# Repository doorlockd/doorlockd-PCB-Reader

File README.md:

## License
Copyright 2021-2025 Matthijs Kooijman (matthijs@stdin.nl)

This source describes Open Hardware and is licensed under the CERN-OHL-P
v2 or any later version.

You may redistribute and modify this documentation and make products
using it under the terms of the CERN-OHL-P v2 (https:/cern.ch/cern-ohl).

This documentation is distributed WITHOUT ANY EXPRESS OR IMPLIED
WARRANTY, INCLUDING OF MERCHANTABILITY, SATISFACTORY QUALITY AND FITNESS
FOR A PARTICULAR PURPOSE. Please see the CERN-OHL-P v2 for applicable
conditions

See LICENSE.txt for the full license text.

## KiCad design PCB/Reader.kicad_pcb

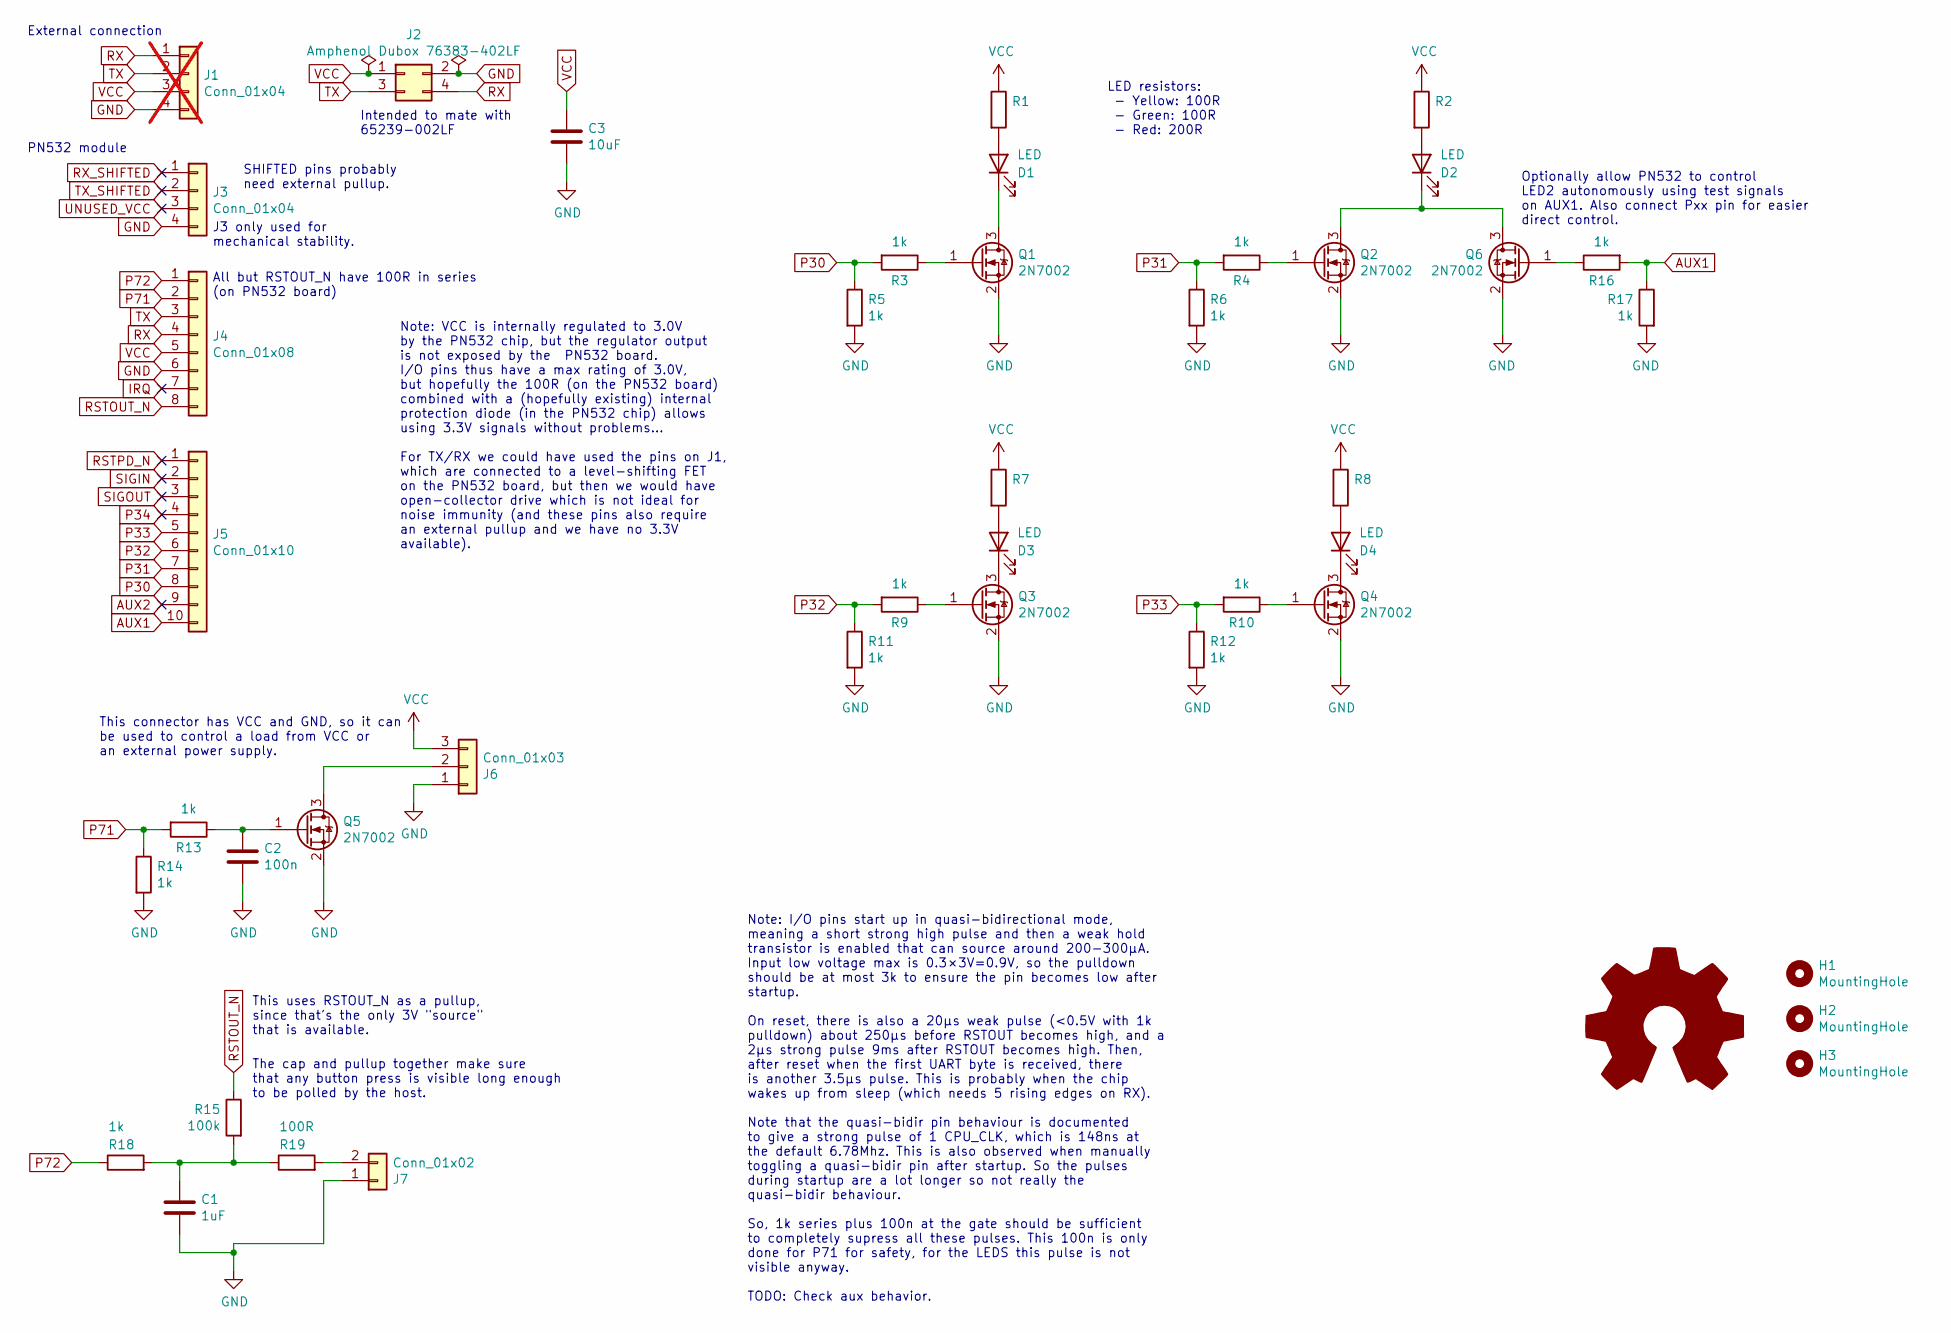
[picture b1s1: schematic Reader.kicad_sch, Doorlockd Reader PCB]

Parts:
C1: 1uF; C_0805_2012Metric_Pad1.18x1.45mm_HandSolder
C2: 100n; C_0805_2012Metric_Pad1.18x1.45mm_HandSolder
C3: 10uF; C_0805_2012Metric_Pad1.18x1.45mm_HandSolder
D1, D2, D3, D4: LED; LED_Rectangular_W5.0mm_H2.0mm
H1, H2, H3: MountingHole; MountingHole_3.2mm_M3
J1: Conn_01x04; PinHeader_1x04_P2.54mm_Vertical; not fitted
J2: Amphenol Dubox ‎76383-402LF‎; PinHeader_2x02_P2.54mm_Horizontal
J3: Conn_01x04; PinSocket_1x04_P2.54mm_Vertical
J4: Conn_01x08; PinSocket_1x08_P2.54mm_Vertical
J5: Conn_01x10; PinSocket_1x10_P1.27mm_Vertical
J6: Conn_01x03; PinHeader_1x03_P2.54mm_Horizontal
J7: Conn_01x02; PinHeader_1x02_P2.54mm_Horizontal
LOGO1: Logo_Open_Hardware_Large; OSHW-Symbol_8.9x8mm_SilkScreen
Q1, Q2, Q3, Q4, Q5, Q6: 2N7002; SOT-23_Handsoldering
R1, R2, R7, R8: R_0805_2012Metric_Pad1.20x1.40mm_HandSolder
R3, R4, R5, R6, R9, R10, R11, R12, R13, R14, R16, R17, R18: 1k; R_0805_2012Metric_Pad1.20x1.40mm_HandSolder
R15: 100k; R_0805_2012Metric_Pad1.20x1.40mm_HandSolder
R19: 100R; R_0805_2012Metric_Pad1.20x1.40mm_HandSolder

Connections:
AUX1: J5.10, R16.2, R17.1
AUX2: J5.9
GND: C1.2, C2.2, C3.2, J1.4, J2.2, J3.4, J4.6, J6.1, J7.1, Q1.2 (S), Q2.2 (S), Q3.2 (S), Q4.2 (S), Q5.2 (S), Q6.2 (S), R5.2, R6.2, R11.2, R12.2, R14.2, R17.2
IRQ: J4.7
unnamed: C1.1, R15.2, R18.2, R19.1
unnamed: D1.2 (A), R1.2
unnamed: D1.1 (K), Q1.3 (D)
unnamed: D2.2 (A), R2.2
unnamed: D2.1 (K), Q2.3 (D), Q6.3 (D)
unnamed: D3.2 (A), R7.2
unnamed: D3.1 (K), Q3.3 (D)
unnamed: D4.2 (A), R8.2
unnamed: D4.1 (K), Q4.3 (D)
unnamed: J6.2, Q5.3 (D)
unnamed: J7.2, R19.2
unnamed: Q1.1 (G), R3.1
unnamed: Q2.1 (G), R4.1
unnamed: Q3.1 (G), R9.1
unnamed: Q4.1 (G), R10.1
unnamed: C2.1, Q5.1 (G), R13.1
unnamed: Q6.1 (G), R16.1
P30: J5.8, R3.2, R5.1
P31: J5.7, R4.2, R6.1
P32: J5.6, R9.2, R11.1
P33: J5.5, R10.2, R12.1
P34: J5.4
P71: J4.2, R13.2, R14.1
P72: J4.1, R18.1
RSTOUT_N: J4.8, R15.1
RSTPD_N: J5.1
RX: J1.1, J2.4, J4.4
RX_SHIFTED: J3.1
SIGIN: J5.2
SIGOUT: J5.3
TX: J1.2, J2.3, J4.3
TX_SHIFTED: J3.2
UNUSED_VCC: J3.3
VCC: C3.1, J1.3, J2.1, J4.5, J6.3, R1.1, R2.1, R7.1, R8.1

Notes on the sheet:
This connector has VCC and GND, so it can be used to control a load from VCC or an external power supply.
Note: VCC is internally regulated to 3.0V by the PN532 chip, but the regulator output is not exposed by the PN532 board. I/O pins thus have a max rating of 3.0V, but hopefully the 100R (on the PN532 board) combined with a (hopefully existing) internal protection diode (in the PN532 chip) allows usi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
LED resistors: - Yellow: 100R - Green: 100R - Red: 200R
Optionally allow PN532 to control LED2 autonomously using test signals on AUX1. Also connect Pxx pin for easier direct control.
This uses RSTOUT_N as a pullup, since that's the only 3V "source" that is available.
PN532 module
SHIFTED pins probably need external pullup.
The cap and pullup together make sure that any button press is visible long enough to be polled by the host.
Note: I/O pins start up in quasi-bidirectional mode, meaning a short strong high pulse and then a weak hold transistor is enabled that can source around 200-300μA. Input low voltage max is 0.3×3V=0.9V, so the pulldown should be at most 3k to ensure the pin becomes low after startup. On reset, there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
J3 only used for mechanical stability.
Intended to mate with 65239-002LF
All but RSTOUT_N have 100R in series (on PN532 board)
External connection

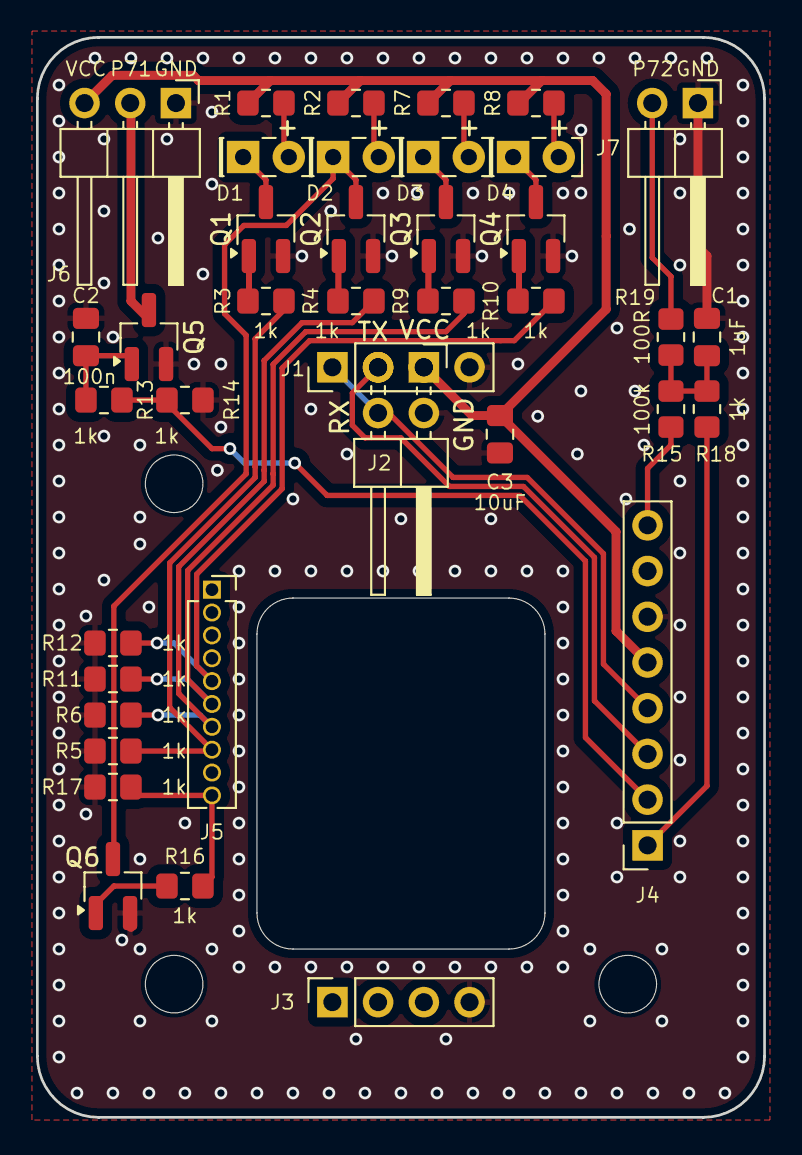
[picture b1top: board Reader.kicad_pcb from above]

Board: 2 copper layers, 40.4 x 60.0 mm, 43 parts (1 on the bottom side), 29 nets.

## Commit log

2021-02-20 Empty initial commit
2021-02-20 Add initial version v0.1
2023-06-06 Update schematic to KiCad 7
    This also sets the edge clearance to 0,5mm. This is a new setting, that
    was previously set using edge cuts line widths and/or zone clearance
    settings. This commit also refills the zones, which are slightly bigger
    than before.
    This also removes the old .sch and .pro file, which are replaced by
    .kicad_sch and .kicad_pro, and removes the lib cache, which is no longer
2023-06-06 Add board name and version to front silkscreen
2023-06-06 Make some schematic changes
    This adds some notes, updates some component values to the actually used
    values, and maybe some other small changes.
2024-01-23 Update PCB from schematic
    This makes no actual changes, just lets KiCad pull in changes (probably
    mostly udpated footprints and renumbered symbols, and maybe some KiCad
    upgrade changes too).
2024-01-23 Add 100n capacitor on output pin
    This takes care of suppressing the startup pulse given by the PN532.
2024-01-23 Add series resistors for button input
2024-02-03 Remove duplicate TODO
2024-02-06 Remove unintended silkscreen line
2024-02-06 Use hand soldering footprints for transistors
2024-02-06 Add input supply buffer cap
2024-02-06 Enlarge mounting holes
2024-02-06 Remove groundloop-related todos
    It seems that having multiple GND connections and a hole inside the GND
    plane might not actually be problematic (or if it is, making a horseshoe
    out of it might not make it better).
    So for now, leave this as is until it is actually a problem.
2024-02-06 Reduce overly wide thermal reliefs due to wide GND traces
    The thermal relief spoke width was 0,3mm, but there were also explicit
    GND traces of 0,5mm that made some components (esp C1 and some
    transistors) hard to solder. This reduces the trace width to 0,3mm,
    hopefully alleviating this issue.
2024-02-06 Mark LED polarity on silkscreen
2024-02-06 Clean up Fab layer
2024-05-28 Improve silkscreen layout
    This also moves some vias, locks some footprints and maybe makes some more changes.
2024-05-28 Update to KiCad 8
    This is the result of opening the project, schematic and board and the
    schematic setup and board setup dialogs (and clicking open each section)
    without making any changes. In addition, a zone fill is done.
    This commit changes all files completely, since the new KiCad adds more
    linebreaks to the files it writes.
2024-05-28 Add changelog file
2024-05-28 Move PCB files into new PCB subdirectory
    This gives a bit more structure to the repository and prepares for
    adding some workflow integration.
2024-05-28 PCB-workflows: Add submodule
2024-05-28 Set up PCB workflow
    This is the result of running `./PCB-workflows/tools/setup-project-repo.sh PCB/Reader.kicad_pro`
2024-10-09 DRC: Enlarge smallest silkscreen text
    The board setup, based on Aisler specifications, has minimum 0.8mm
    height for text. This changes most text that uses 0.75mm to use 0.8mm
    instead. No text is moved, this just enlarges the text slightly (by
    manually editing the kicad_pcb file).
2024-10-09 DRC: Exclude three GND pins with too few thermals
    These have a good connection on the bottom, just too little connection
    on the top, but since there is little GND plane on the top to connect
    to, this is not an issue.
2024-10-09 DRC: Remove random silkscreen lines
2024-10-09 DRC: Update footprints from library
2024-10-09 Set up PCB workflow
    This is the result of running
    `./PCB-workflows/tools/setup-project-repo.sh PCB/Reader.kicad_pro` and
    then changing the page setup to use the drawing sheet without 3devo
    logo.
2024-10-09 More KiCad 8 updates to project file
    These were written by KiCad 8 after opening the board contstraints and
    adding some DRC exceptions (so either of those triggered this).
2024-10-09 ERC: Add power flag for GND and VCC inputs
    This fixes the last ERC errors
2024-10-09 DRC: Ignore overlapping courtyards and silkscreen
    This is a tiny PCB, so there are a dozen of overlapping courtyards and
    silkscreen that are acceptable and unavoidable, so just ignore all of them.
2024-10-09 ERC: Update schematic symbols from library
2024-10-09 DRC: Ignore two overlapping hole warnings
    This is from two footprints that intentionally overlap, so this is ok.
    Note that when running DRC with KiCad 8.0.2, these exceptions seem to be
    dropped and these errors re-occur for some reason. This is probably
    a KiCad bug.
2024-10-09 DRC: (Re)move two vias
    Seems tracks were moved over/near these vias, producing a short and
    clearance failure. This removes one via and moves the other.
2024-10-09 ERC: Ignore missing spice models
2024-10-09 DRC: Slightly reduce center hole size
    This ensurs the connector silkscreen is not cut off by the board edge,
    fixing a bunch of DRC warnings.
2024-10-09 ERC: Add NC flags for unused pins
2024-10-10 Move schematic note onto page
2024-10-10 Improve some schematic notes
2024-11-21 Small layout and via improvements
    This also makes some changes that are likely because of using a slightly
    newer KiCad version.
2024-11-21 Replace LED resistor values with lookup table
2024-11-21 Improve revision silk and re-add OSHW logo
    The logo got removed at some point, so re-add it.
    Remove the PCB name on the front in favor of the silk on the back where
    there is more room.
    Match the PCB name to the git repo name, and auto-fill the board
    revision.
2024-11-21 Update PCB from schematic
    This makes some property changes, but does not update anything
    functionally.
2024-11-21 Add note about not using the level shifted pins
2025-01-02 PCB-workflows: Update
    This includes the following commits:
    89ca71b Workaround kibot issue that causes build to fail
    add74d3 Switch to KiCad 8 erc/drc checks
2025-01-07 DRC: Slightly reduce center hole size
    This ensures the connector silkscreen is not cut off by the board edge,
    fixing a bunch of DRC warnings.
2025-01-08 PCB-workflows: Update
    This includes the following commits:
    89ca71b Workaround kibot issue that causes build to fail
    add74d3 Switch to KiCad 8 erc/drc checks
    032b730 Grant permissions to create releases
    6fca111 Remove outdated comment
    ff02ff5 Generate gerbers and drill files for JLPCB
2025-01-08 Give workflow permission to create releases
    The organisation default is apparently read-only (now) GITHUB_TOKEN, so
    instead of changing that globally, change it just for this workflow job.
2025-01-08 Use CERN-OHL-P v2+ license
2025-01-08 Do a zone fill
    Seems some (subtle?) copper changes were not applied in some earlier
    commit.not applied in some earlier commit.not applied in some earlier
    commit.not applied in some earlier commit.
2025-01-08 Mark 4-pin J1 pin header as DNP
    This pin header is an alternative for the J2 2x2 pin connector and the
    footprint is added just in case, but normally only J2 should be used.
2025-01-08 Improve dimension annotations
    This is mostly layout fixes (fix overlapping numbers, smaller arrows and
    less decimals), but also fixes the annotation of the center cutout which
    was a little misaligned, probably after commit a628468 (DRC: Slightly
    reduce center hole size, 2024-07-09).
2025-01-08 Add README
2025-01-08 Complete and improve changelog
2025-01-08 Release v1.0
2025-01-08 Add some (estethic) structure to the schematic

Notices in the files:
PCB/Reader.kicad_pcb:
Licensed under CERN-OHL-P v2 or any later version
